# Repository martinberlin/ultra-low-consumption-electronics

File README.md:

# ultra-low-consumption-electronics
Here we will make electronic experiments to try reaching the lowest possible consumption when dealing with Microcontrollers and small Lithium batteries, turning when possible everything OFF

## Parts will be a shared folder between different PCBs

The parts folder will contain common Symbols, Footprints and 3D models.

## 1st. experiment: RV3032 application manual page 144

RV3032 is a DTCXO Temp. Compensated Real-Time Clock Module
Based on App. Manual released on May 2023 144/154 Rev. 1.3

**8.5. NO BACKUP SOURCE / EVENT INPUT USED ("WAKE-UP" & "POWER SWITCH")**

WARNING:
 This are theoretical ideas that could mainly be untested. Use any of them on production at your own risk.

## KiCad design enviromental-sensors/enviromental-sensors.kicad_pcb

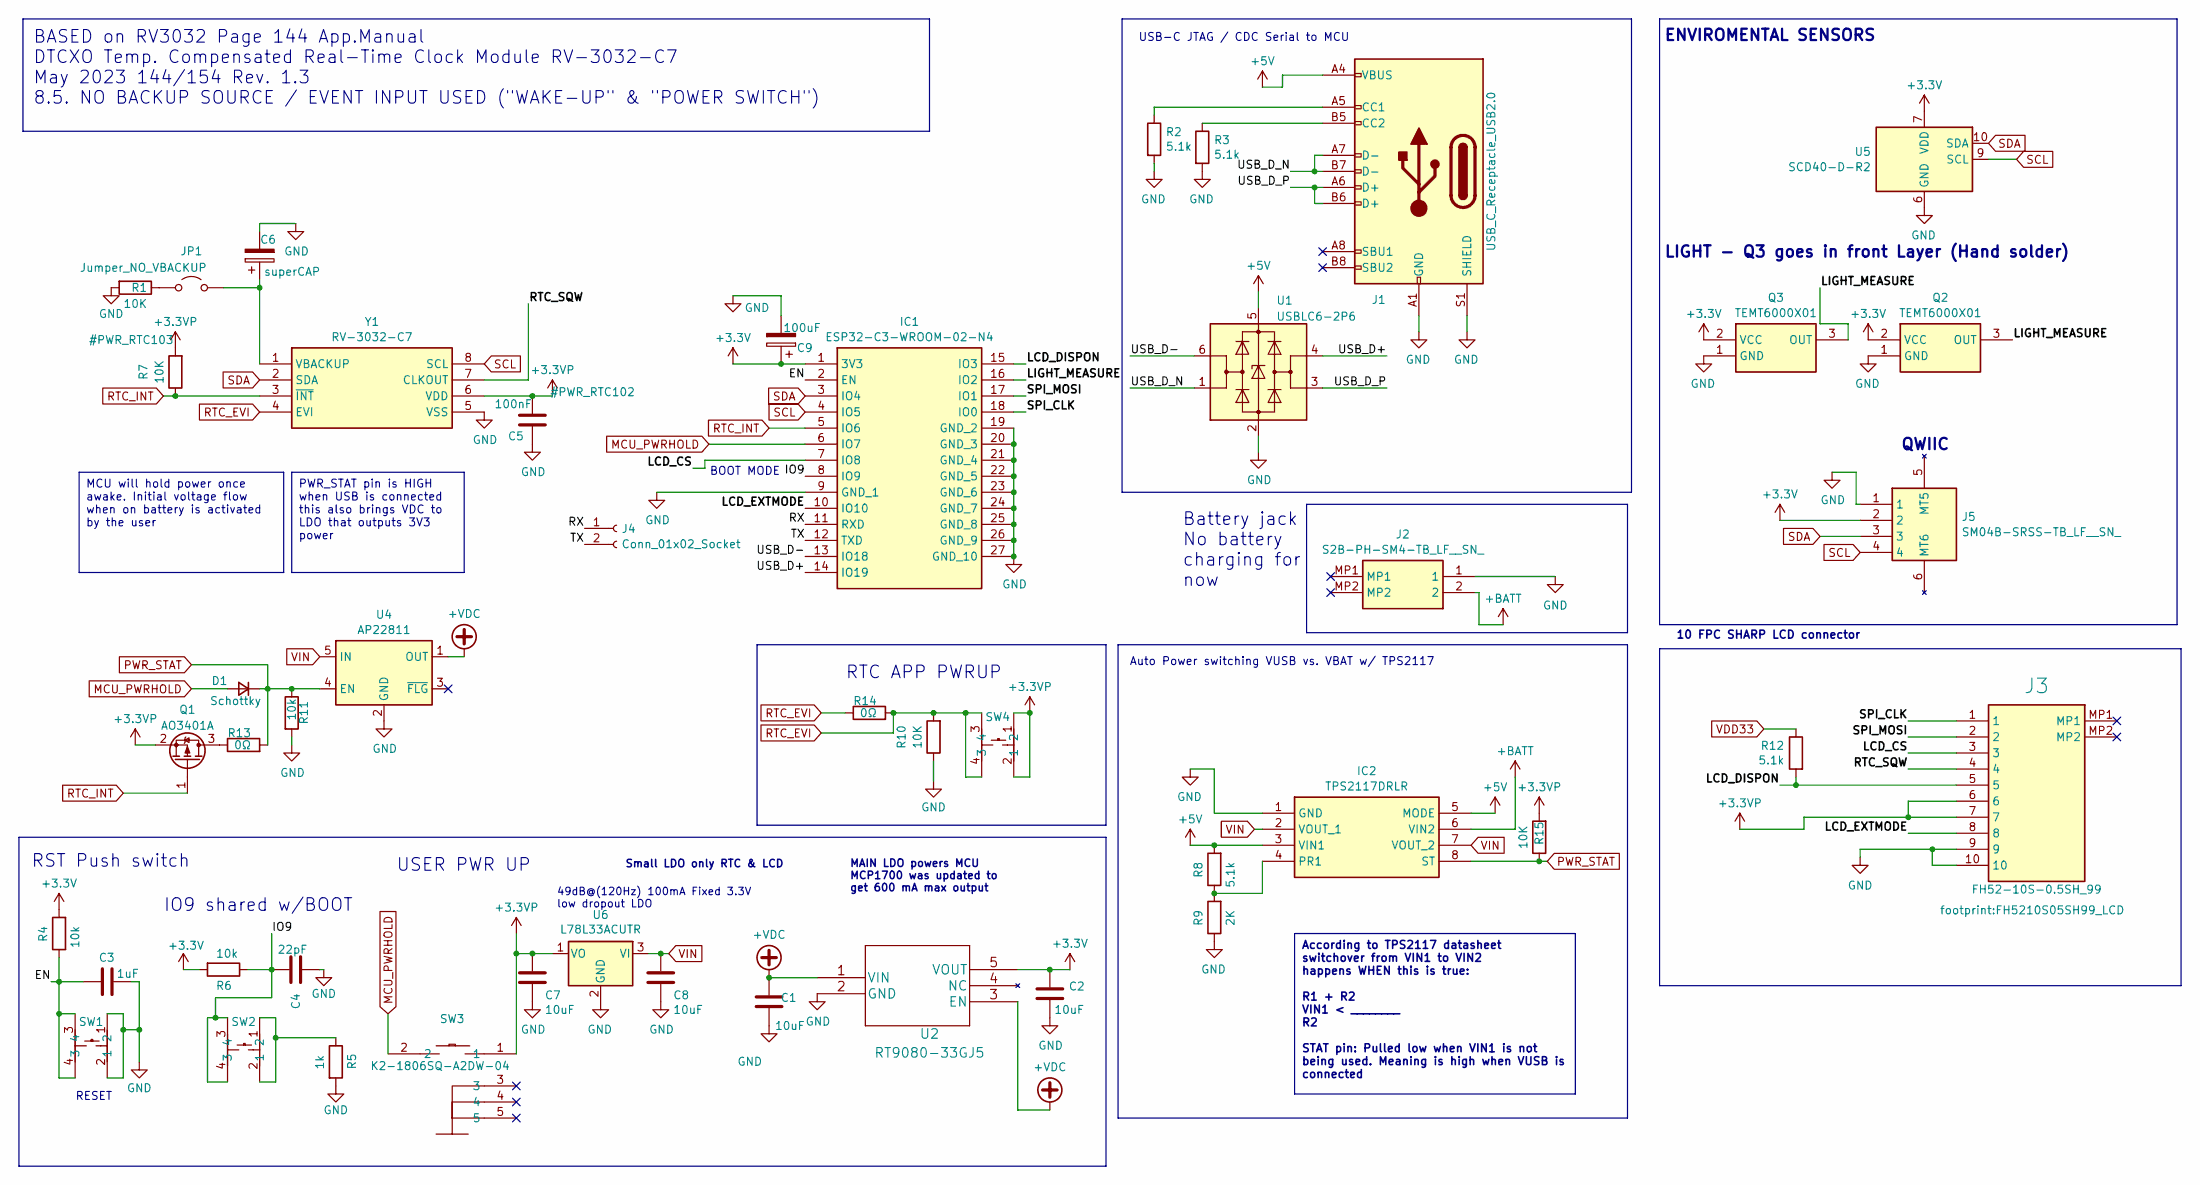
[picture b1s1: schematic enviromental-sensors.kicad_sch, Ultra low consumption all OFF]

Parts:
C1, C2, C7, C8: 10uF; C_0805_2012Metric; LCSC C15850
C3: 1uF; C_0402_1005Metric; LCSC C162161
C4: 22pF; C_0402_1005Metric; LCSC C5119318
C5: 100nF; C_0805_2012Metric; LCSC C49678
C6: superCAP; C9900013866_SUPERCAP-TH_XH414HG; LCSC C9900013866
C9: 100uF; CP_EIA-3528-15_AVX-H; LCSC C16133
D1: Schottky; D_SOD-123; LCSC C8598
IC1: ESP32-C3-WROOM-02-N4; ESP32C3WROOM02N4; LCSC C2934560
IC2: TPS2117DRLR; C22399676_TPS2117-8N; LCSC C22399676
J1: USB_C_Receptacle_USB2.0; USB_C_Receptacle_HRO_TYPE-C-31-M-12; LCSC C165948
J2: S2B-PH-SM4-TB_LF__SN_; S2BPHSM4TBLFSN; Manufacturer_Part_Number S2B-PH-SM4-TB(LF)(SN); LCSC C295747
J3: FH52-10S-0.5SH_99; FH5210S05SH99_LCD; Manufacturer_Part_Number FH52-10S-0.5SH(99); JLCPCB Part # C598038
J4: Conn_01x02_Socket; PinHeader_1x02_P2.54mm_Vertical
J5: SM04B-SRSS-TB_LF__SN_; QWIIC_SM04B-SRSS-TB_LFSN_; Manufacturer_Part_Number SM04B-SRSS-TB(LF)(SN); LCSC C160404
JP1: Jumper_NO_VBACKUP; SolderJumper-2_P1.3mm_Open_RoundedPad1.0x1.5mm
Q1: AO3401A; SOT-23; LCSC C15127
Q2, Q3: TEMT6000X01; LCSC C94098
R1, R7, R10, R15: 10K; R_0603_1608Metric; LCSC C25804
R2, R3, R8, R12: 5.1k; R_0603_1608Metric; LCSC C23186
R4, R6: 10k; R_0402_1005Metric; LCSC C4322213
R5: 1k; R_0603_1608Metric; LCSC C21190
R9: 2K; R_0603_1608Metric; LCSC C22975
R11: 10k; R_0603_1608Metric; LCSC C25804
R13: 0Ω; R_0603_1608Metric; LCSC C25804
R14: 0Ω; R_0603_1608Metric; LCSC C21189
SW1, SW2, SW4: TC-0522C-1.7-160G; C2845289_SW-SMD_4P-L5.2-W5.2-P3.70-LS6.4; LCSC Part C2845289
SW3: K2-1806SQ-A2DW-04; C5143621_KEY-SMD_TS24ZJ; LCSC Part C19100323
U1: USBLC6-2P6; SOT-666; LCSC C2827693
U2: RT9080-33GJ5; TSOT-23-5; LCSC C841192
U4: AP22811; C3001660_SOT95P285X140-5N; LCSC C3001660
U5: SCD40-D-R2; Sensirion_SCD4x-1EP_10.1x10.1mm_P1.25mm_EP4.8x4.8mm; LCSC C3659421
U6: L78L33ACUTR; SOT-89-3; LCSC C14170
Y1: RV-3032-C7; RV3032C7; LCSC C5127802

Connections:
+3.3V: C2.2, C9.1, IC1.1 (3V3), J5.2, Q2.2 (VCC), Q3.2 (VCC), R4.2, R6.2, U2.5 (VOUT), U5.7 (VDD), U5.19 (VDD)
+3.3VP: C5.1, C7.2, J3.6, J3.7, Q1.2 (S), R7.2, R15.2, SW3.1, SW4.1, SW4.2, U6.1 (VO), Y1.6 (VDD)
+5V: IC2.3 (VIN1), IC2.5 (MODE), J1.A4 (VBUS), J1.A9 (VBUS), J1.B4 (VBUS), J1.B9 (VBUS), R8.2, U1.5 (VBUS)
+BATT: IC2.6 (VIN2), J2.2
+VDC: C1.1, U2.1 (VIN), U2.3 (EN), U4.1 (OUT)
/EN: C3.2, IC1.2 (EN), R4.1, SW1.3, SW1.4
/IO9: C4.2, IC1.8 (IO9), R6.1, SW2.3, SW2.4
/LCD_CS: IC1.7 (IO8), J3.3
/LCD_DISPON: IC1.15 (IO3), J3.5, R12.2
/LCD_EXTMODE: IC1.10 (IO10), J3.8
/LIGHT_MEASURE: IC1.16 (IO2), Q2.3 (OUT), Q3.3 (OUT)
/RTC_SQW: J3.4, Y1.7 (CLKOUT)
/RX: IC1.11 (RXD), J4.1
/SPI_CLK: IC1.18 (IO0), J3.1
/SPI_MOSI: IC1.17 (IO1), J3.2
/TX: IC1.12 (TXD), J4.2
/USB_D+: IC1.14 (IO19), U1.4 (I/O2)
/USB_D-: IC1.13 (IO18), U1.6 (I/O1)
/USB_D_N: J1.A7 (D-), J1.B7 (D-), U1.1 (I/O1)
/USB_D_P: J1.A6 (D+), J1.B6 (D+), U1.3 (I/O2)
GND: C1.2, C2.1, C3.1, C4.1, C5.2, C6.2, C7.1, C8.1, C9.2, IC1.9 (GND_1), IC1.19 (GND_2), IC1.20 (GND_3), IC1.21 (GND_4), IC1.22 (GND_5), IC1.23 (GND_6), IC1.24 (GND_7), IC1.25 (GND_8), IC1.26 (GND_9), IC1.27 (GND_10), IC2.1 (GND), J1.A1 (GND), J1.A12 (GND), J1.B1 (GND), J1.B12 (GND), J1.S1 (SHIELD), J2.1, J3.9, J3.10, J5.1, Q2.1 (GND), Q3.1 (GND), R1.2, R2.2, R3.2, R5.2, R9.1, R10.1, R11.2, SW1.1, SW1.2, U1.2 (GND), U2.2 (GND), U4.2 (GND), U5.6 (GND), U5.20 (GND), U5.21 (GND), U6.2 (GND), Y1.5 (VSS)
MCU_PWRHOLD: D1.2 (A), IC1.6 (IO7), SW3.2
unnamed: IC2.4 (PR1), R8.1, R9.2
unnamed: J1.A5 (CC1), R2.1
unnamed: J1.B5 (CC2), R3.1
unnamed: JP1.1 (A), R1.1
unnamed: C6.1, JP1.2 (B), Y1.1 (VBACKUP)
unnamed: Q1.3 (D), R13.1
unnamed: R5.1, SW2.1, SW2.2
PWR_STAT: D1.1 (K), IC2.8 (ST), R11.1, R13.2, R15.1, U4.4 (EN)
RTC_EVI: R10.2, R14.1, R14.2, SW4.3, SW4.4, Y1.4 (EVI)
RTC_INT: IC1.5 (IO6), Q1.1 (G), R7.1, Y1.3 (~INT)
SCL: IC1.4 (IO5), J5.4, U5.9 (SCL), Y1.8 (SCL)
SDA: IC1.3 (IO4), J5.3, U5.10 (SDA), Y1.2 (SDA)
VDD33: R12.1
VIN: C8.2, IC2.2 (VOUT_1), IC2.7 (VOUT_2), U4.5 (IN), U6.3 (VI)

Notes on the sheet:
MCU will hold power once awake. Initial voltage flow when on battery is activated by the user
BASED on RV3032 Page 144 App.Manual DTCXO Temp. Compensated Real-Time Clock Module RV-3032-C7 May 2023 144/154 Rev. 1.3 8.5. NO BACKUP SOURCE / EVENT INPUT USED ("WAKE-UP" & "POWER SWITCH")
PWR_STAT pin is HIGH when USB is connected this also brings VDC to LDO that outputs 3V3 power
According to TPS2117 datasheet switchover from VIN1 to VIN2 happens WHEN this is true: R1 + R2 VIN1 < ________ R2 STAT pin: Pulled low when VIN1 is not being used. Meaning is high when VUSB is connected
ENVIROMENTAL SENSORS
IO9 shared w/BOOT
USER PWR UP
USB-C JTAG / CDC Serial to MCU
RST Push switch
RESET
RTC APP PWRUP
Small LDO only RTC & LCD
49dB@(120Hz) 100mA Fixed 3.3V low dropout LDO
Auto Power switching VUSB vs. VBAT w/ TPS2117
Battery jack No battery charging for now
LIGHT - Q3 goes in front Layer (Hand solder)
QWIIC
BOOT MODE
10 FPC SHARP LCD connector
MAIN LDO powers MCU MCP1700 was updated to get 600 mA max output

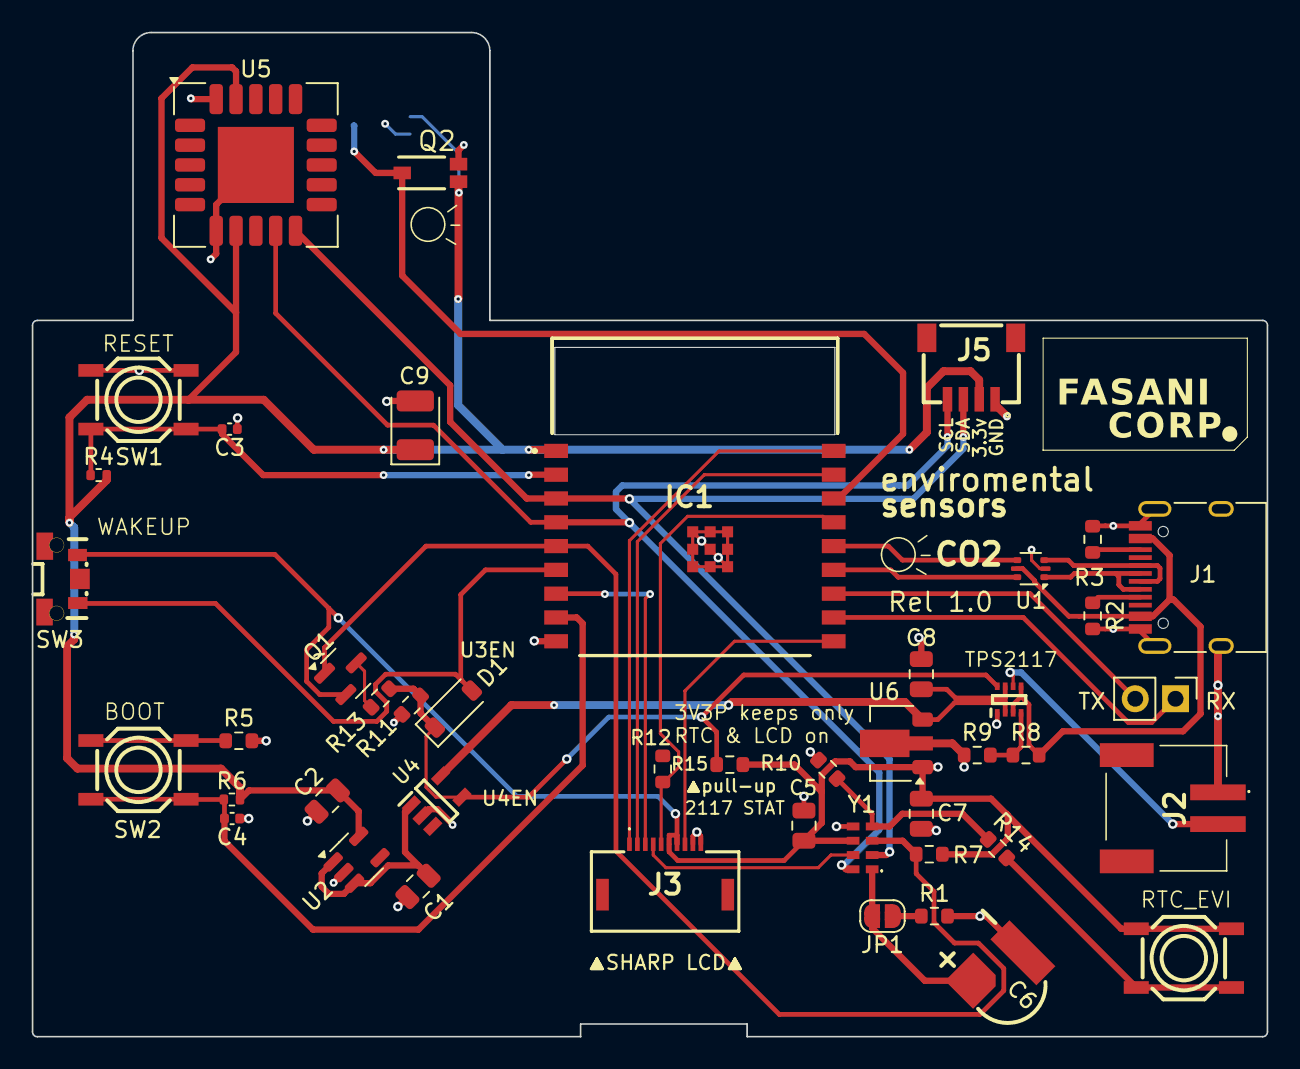
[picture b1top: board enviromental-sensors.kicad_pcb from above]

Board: 2 copper layers, 77.9 x 63.3 mm, 46 parts (1 on the bottom side), 35 nets.

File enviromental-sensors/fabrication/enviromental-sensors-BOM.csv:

Designator,Footprint,Comment,JLCPCB Part #
J1,USB_C_Receptacle_HRO_TYPE-C-31-M-12,USB_C_Receptacle_USB2.0,C165948
"C2,C8,C7,C1",C_0805_2012Metric,10uF,C15850
Y1,RV3032C7,RV-3032-C7,C5127802
R5,R_0603_1608Metric,1k,C21190
"SW4,SW2,SW1",C2845289_SW-SMD_4P-L5.2-W5.2-P3.70-LS6.4,TC-0522C-1.7-160G,C2845289
U6,SOT-89-3,L78L33ACUTR,C14170
J3,FH5210S05SH99_LCD,FH52-10S-0.5SH_99,C598038
"R2,R12,R8,R3",R_0603_1608Metric,5.1k,C23186
"R1,R10,R7",R_0603_1608Metric,10K,C25804
Q1,SOT-23,AO3401A,C15127
U5,Sensirion_SCD4x-1EP_10.1x10.1mm_P1.25mm_EP4.8x4.8mm,SCD40-D-R2,C3659421
U4,C3001660_SOT95P285X140-5N,AP22811,C3001660
U2,SOT-23-5,RT9080,C841192
R9,R_0603_1608Metric,2K,C22975
D1,D_SOD-123,Schottky,C8598
IC2,C22399676_TPS2117-8N,TPS2117DRLR,C22399676
C3,C_0402_1005Metric,1uF,C162161
C4,C_0402_1005Metric,22pF,C5119318
SW3,C5143621_KEY-SMD_TS24ZJ,K2-1806SQ-A2DW-04,C19100323
C5,C_0805_2012Metric,100nF,C49678
R14,R_0603_1608Metric,0Ω,C21189
"R4,R6",R_0402_1005Metric,10k,C4322213
J2,S2BPHSM4TBLFSN,S2B-PH-SM4-TB_LF__SN_,C295747
C9,CP_EIA-3528-15_AVX-H,100uF,C16133
R13,R_0603_1608Metric,0Ω,C21189
R11,R_0603_1608Metric,10k,C25804
U1,SOT-666,USBLC6-2P6,C2827693
Q2,TEMT6000X01,TEMT6000X01,C94098
J5,SM04B-SRSS-TB_LF__SN_,JST connector,C160404

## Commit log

2025-03-12 Add SuperCAP to RTC
2025-03-12 Update schematics
2025-03-13 Correct C5
2025-03-13 Add EVI app PWR up
2025-03-13 Create LICENSE
2025-03-14 1.0 passes DRC
2025-03-15 Update U3
2025-03-15 Correct Q1. Thanks Syl!
2025-03-15 Put some love in silk
2025-03-17 Last revision before 1.0
2025-03-17 Update SCH
2025-03-19 Add env. sensors PCB
2025-04-04 1.0 fixes: QWIIC corrected (note 1.0 release before this commit is unfixed)
